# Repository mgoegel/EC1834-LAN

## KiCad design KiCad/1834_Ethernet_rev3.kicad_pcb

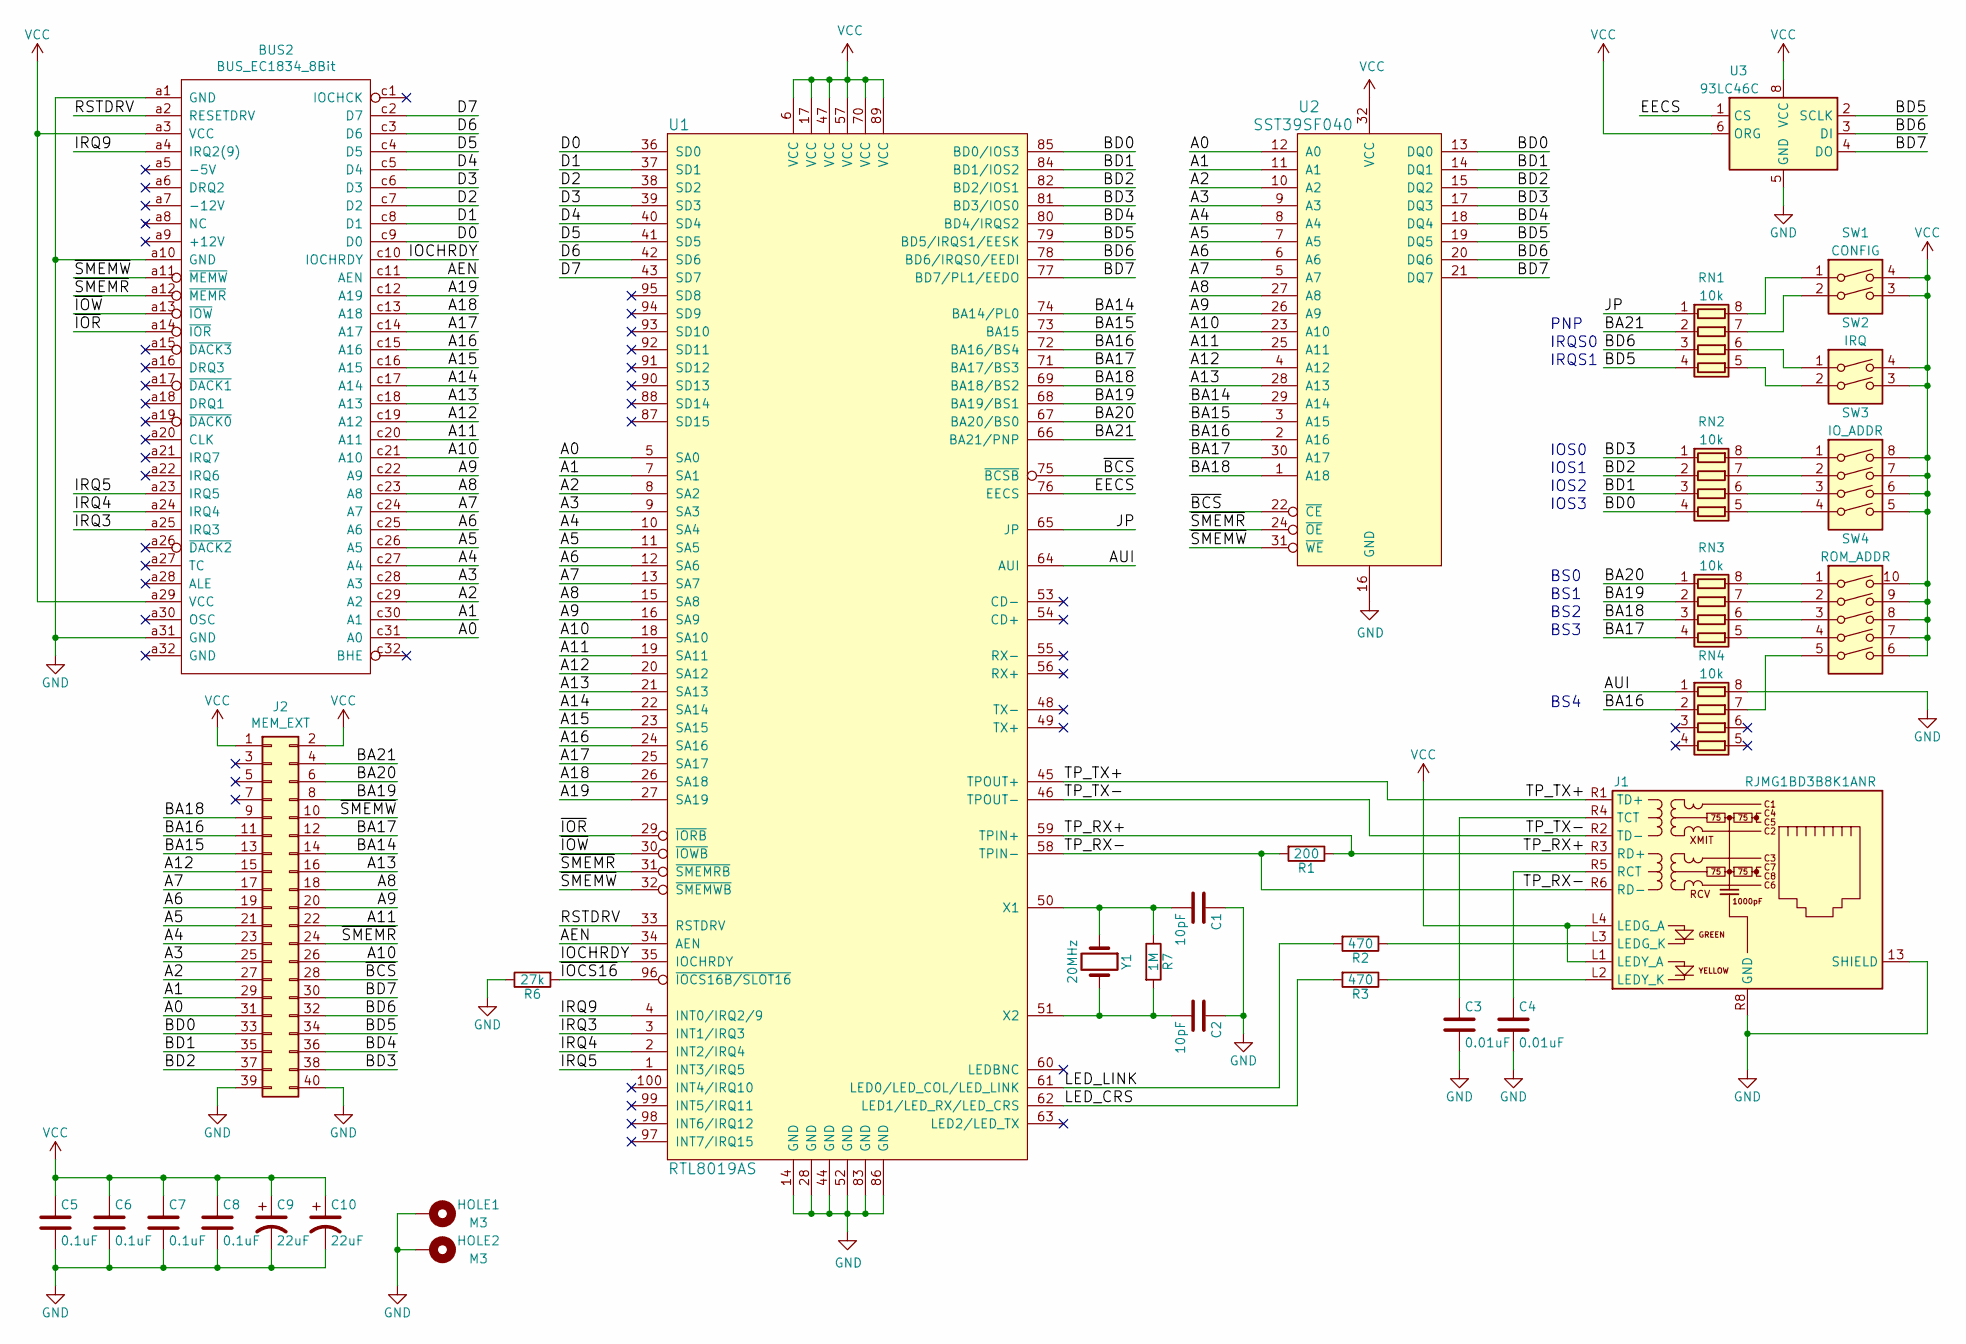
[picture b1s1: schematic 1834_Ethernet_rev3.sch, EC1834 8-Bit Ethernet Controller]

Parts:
BUS2: BUS_EC1834_8Bit; DIN41612_C_3x32_Male_Horizontal_THT
C1, C2: 10pF; C_0603_1608Metric_Pad1.08x0.95mm_HandSolder
C3, C4: 0.01uF; C_0603_1608Metric_Pad1.08x0.95mm_HandSolder
C5, C6, C7, C8: 0.1uF; C_0603_1608Metric_Pad1.08x0.95mm_HandSolder
C9, C10: 22uF; CP_EIA-3528-15_AVX-H_Pad1.50x2.35mm_HandSolder
HOLE1, HOLE2: M3; MountingHole_3.2mm_M3_Pad_Via
J1: RJMG1BD3B8K1ANR; RJ45_Amphenol_RJMG1BD3B8K1ANR
J2: MEM_EXT; Conn_Pin_Header_20x2_2.54mm
R1: 200; R_0603_1608Metric_Pad0.98x0.95mm_HandSolder
R2, R3: 470; R_0603_1608Metric_Pad0.98x0.95mm_HandSolder
R6: 27k; R_0603_1608Metric_Pad0.98x0.95mm_HandSolder
R7: 1M; R_0603_1608Metric_Pad0.98x0.95mm_HandSolder
RN1, RN2, RN3, RN4: 10k; R_Array_Convex_4x0603
SW1: CONFIG; Switch_DIP_2_Positions
SW2: IRQ; Switch_DIP_2_Positions
SW3: IO_ADDR; Switch_DIP_4_Positions
SW4: ROM_ADDR; Switch_DIP_5_Positions
U1: RTL8019AS; IC_PQFP-100_14x20mm_P0.65mm_Hand_Soldering
U2: SST39SF040; Socket_DIP32_600
U3: 93LC46C; SO-8_3.9x4.9mm_P1.27mm
Y1: 20MHz; Crystal_HC-49U_Vert

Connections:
/A0: BUS2.c31 (A0), J2.31, U1.5 (SA0), U2.12 (A0)
/A1: BUS2.c30 (A1), J2.29, U1.7 (SA1), U2.11 (A1)
/A2: BUS2.c29 (A2), J2.27, U1.8 (SA2), U2.10 (A2)
/A3: BUS2.c28 (A3), J2.25, U1.9 (SA3), U2.9 (A3)
/A4: BUS2.c27 (A4), J2.23, U1.10 (SA4), U2.8 (A4)
/A5: BUS2.c26 (A5), J2.21, U1.11 (SA5), U2.7 (A5)
/A6: BUS2.c25 (A6), J2.19, U1.12 (SA6), U2.6 (A6)
/A7: BUS2.c24 (A7), J2.17, U1.13 (SA7), U2.5 (A7)
/A8: BUS2.c23 (A8), J2.18, U1.15 (SA8), U2.27 (A8)
/A9: BUS2.c22 (A9), J2.20, U1.16 (SA9), U2.26 (A9)
/A10: BUS2.c21 (A10), J2.26, U1.18 (SA10), U2.23 (A10)
/A11: BUS2.c20 (A11), J2.22, U1.19 (SA11), U2.25 (A11)
/A12: BUS2.c19 (A12), J2.15, U1.20 (SA12), U2.4 (A12)
/A13: BUS2.c18 (A13), J2.16, U1.21 (SA13), U2.28 (A13)
/A14: BUS2.c17 (A14), U1.22 (SA14)
/A15: BUS2.c16 (A15), U1.23 (SA15)
/A16: BUS2.c15 (A16), U1.24 (SA16)
/A17: BUS2.c14 (A17), U1.25 (SA17)
/A18: BUS2.c13 (A18), U1.26 (SA18)
/A19: BUS2.c12 (A19), U1.27 (SA19)
/AEN: BUS2.c11 (AEN), U1.34 (AEN)
/AUI: RN4.1 (R1.1), U1.64 (AUI)
/BA14: J2.14, U1.74 (BA14/PL0), U2.29 (A14)
/BA15: J2.13, U1.73 (BA15), U2.3 (A15)
/BA16: J2.11, RN4.2 (R2.1), U1.72 (BA16/BS4), U2.2 (A16)
/BA17: J2.12, RN3.4 (R4.1), U1.71 (BA17/BS3), U2.30 (A17)
/BA18: J2.9, RN3.3 (R3.1), U1.69 (BA18/BS2), U2.1 (A18)
/BA19: J2.8, RN3.2 (R2.1), U1.68 (BA19/BS1)
/BA20: J2.6, RN3.1 (R1.1), U1.67 (BA20/BS0)
/BA21: J2.4, RN1.2 (R2.1), U1.66 (BA21/PNP)
/BD0: J2.33, RN2.4 (R4.1), U1.85 (BD0/IOS3), U2.13 (DQ0)
/BD1: J2.35, RN2.3 (R3.1), U1.84 (BD1/IOS2), U2.14 (DQ1)
/BD2: J2.37, RN2.2 (R2.1), U1.82 (BD2/IOS1), U2.15 (DQ2)
/BD3: J2.38, RN2.1 (R1.1), U1.81 (BD3/IOS0), U2.17 (DQ3)
/BD4: J2.36, U1.80 (BD4/IRQS2), U2.18 (DQ4)
/BD5: J2.34, RN1.4 (R4.1), U1.79 (BD5/IRQS1/EESK), U2.19 (DQ5), U3.2 (SCLK)
/BD6: J2.32, RN1.3 (R3.1), U1.78 (BD6/IRQS0/EEDI), U2.20 (DQ6), U3.3 (DI)
/BD7: J2.30, U1.77 (BD7/PL1/EEDO), U2.21 (DQ7), U3.4 (DO)
/D0: BUS2.c9 (D0), U1.36 (SD0)
/D1: BUS2.c8 (D1), U1.37 (SD1)
/D2: BUS2.c7 (D2), U1.38 (SD2)
/D3: BUS2.c6 (D3), U1.39 (SD3)
/D4: BUS2.c5 (D4), U1.40 (SD4)
/D5: BUS2.c4 (D5), U1.41 (SD5)
/D6: BUS2.c3 (D6), U1.42 (SD6)
/D7: BUS2.c2 (D7), U1.43 (SD7)
/EECS: U1.76 (EECS), U3.1 (CS)
/IOCHRDY: BUS2.c10 (IOCHRDY), U1.35 (IOCHRDY)
/IRQ3: BUS2.a25 (IRQ3), U1.3 (INT1/IRQ3)
/IRQ4: BUS2.a24 (IRQ4), U1.2 (INT2/IRQ4)
/IRQ5: BUS2.a23 (IRQ5), U1.1 (INT3/IRQ5)
/IRQ9: BUS2.a4 (IRQ2(9)), U1.4 (INT0/IRQ2/9)
/JP: RN1.1 (R1.1), U1.65 (JP)
/LED_CRS: R3.2, U1.62 (LED1/LED_RX/LED_CRS)
/LED_LINK: R2.2, U1.61 (LED0/LED_COL/LED_LINK)
/RSTDRV: BUS2.a2 (RESETDRV), U1.33 (RSTDRV)
/TP_RX+: J1.R3 (RD+), R1.1, U1.59 (TPIN+)
/TP_RX-: J1.R6 (RD-), R1.2, U1.58 (TPIN-)
/TP_TX+: J1.R1 (TD+), U1.45 (TPOUT+)
/TP_TX-: J1.R2 (TD-), U1.46 (TPOUT-)
/~BCS: J2.28, U1.75 (~BCSB), U2.22 (~CE)
/~IOCS16: R6.2, U1.96 (~IOCS16B/SLOT16)
/~IOR: BUS2.a14 (~IOR), U1.29 (~IORB)
/~IOW: BUS2.a13 (~IOW), U1.30 (~IOWB)
/~SMEMR: BUS2.a12 (~MEMR), J2.24, U1.31 (~SMEMRB), U2.24 (~OE)
/~SMEMW: BUS2.a11 (~MEMW), J2.10, U1.32 (~SMEMWB), U2.31 (~WE)
GND: BUS2.a1 (GND), BUS2.a10 (GND), BUS2.a31 (GND), C1.1, C2.1, C3.2, C4.2, C5.2, C6.2, C7.2, C8.2, C9.2, C10.2, HOLE1.1, HOLE2.1, J1.13 (SHIELD), J1.R8 (GND), J2.39, J2.40, R6.1, RN4.8 (R1.2), U1.14 (GND), U1.28 (GND), U1.44 (GND), U1.52 (GND), U1.83 (GND), U1.86 (GND), U2.16 (GND), U3.5 (GND)
unnamed: C1.2, R7.1, U1.50 (X1), Y1.1
unnamed: C2.2, R7.2, U1.51 (X2), Y1.2
unnamed: C3.1, J1.R4 (TCT)
unnamed: C4.1, J1.R5 (RCT)
unnamed: J1.L2 (LEDY_K), R3.1
unnamed: J1.L3 (LEDG_K), R2.1
unnamed: RN1.5 (R4.2), SW2.2
unnamed: RN1.6 (R3.2), SW2.1
unnamed: RN1.7 (R2.2), SW1.2
unnamed: RN1.8 (R1.2), SW1.1
unnamed: RN2.5 (R4.2), SW3.4
unnamed: RN2.6 (R3.2), SW3.3
unnamed: RN2.7 (R2.2), SW3.2
unnamed: RN2.8 (R1.2), SW3.1
unnamed: RN3.5 (R4.2), SW4.4
unnamed: RN3.6 (R3.2), SW4.3
unnamed: RN3.7 (R2.2), SW4.2
unnamed: RN3.8 (R1.2), SW4.1
unnamed: RN4.7 (R2.2), SW4.5
VCC: BUS2.a3 (VCC), BUS2.a29 (VCC), C5.1, C6.1, C7.1, C8.1, C9.1, C10.1, J1.L1 (LEDY_A), J1.L4 (LEDG_A), J2.1, J2.2, SW1.3, SW1.4, SW2.3, SW2.4, SW3.5, SW3.6, SW3.7, SW3.8, SW4.6, SW4.7, SW4.8, SW4.9, SW4.10, U1.6 (VCC), U1.17 (VCC), U1.47 (VCC), U1.57 (VCC), U1.70 (VCC), U1.89 (VCC), U2.32 (VCC), U3.6 (ORG), U3.8 (VCC)

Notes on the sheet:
IOS0
IOS1
IOS2
IOS3
IRQS0
IRQS1
BS4
BS3
BS2
BS1
BS0
PNP

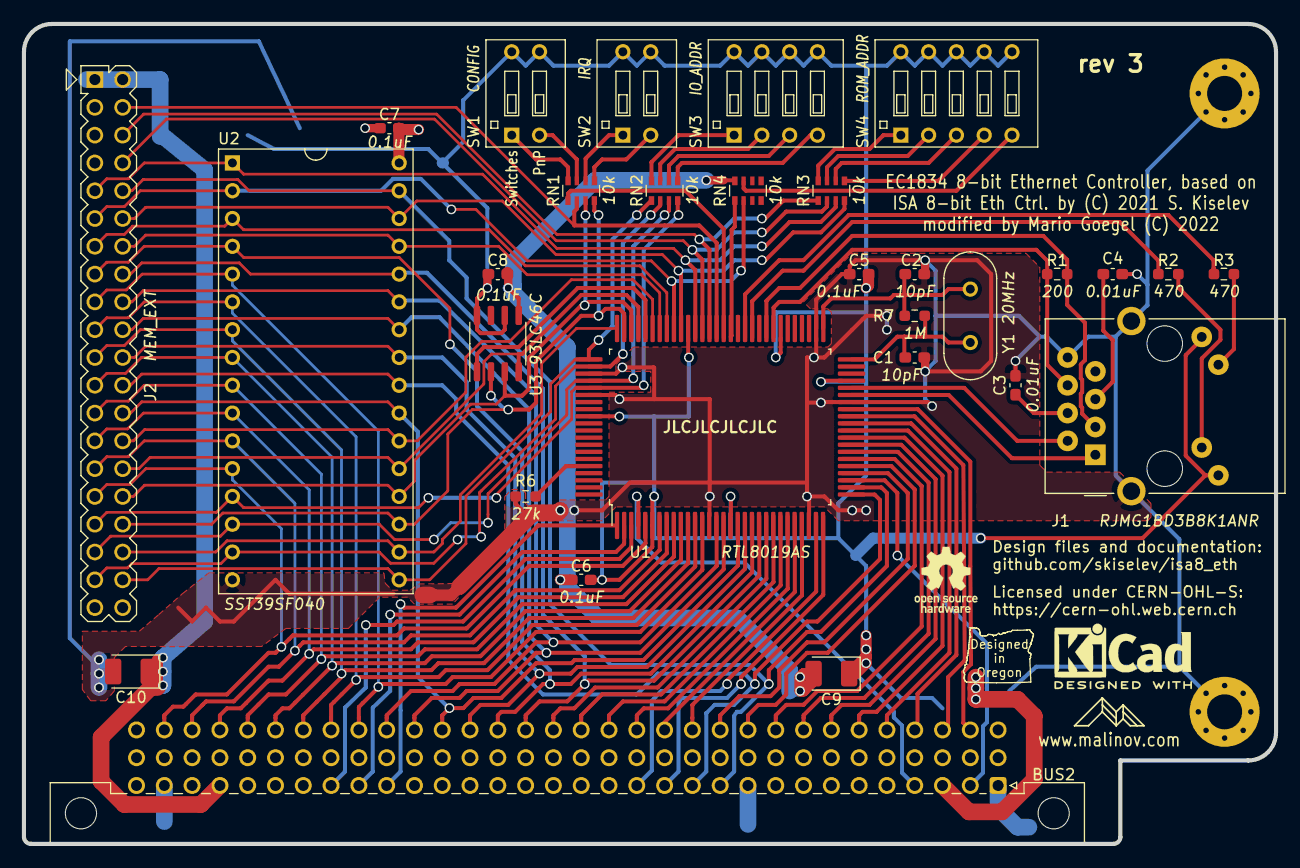
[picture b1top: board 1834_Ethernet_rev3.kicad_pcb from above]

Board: 2 copper layers, 114.4 x 74.9 mm, 32 parts (0 on the bottom side), 87 nets.

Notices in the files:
KiCad/1834_Ethernet_rev3.kicad_pcb:
Licensed under CERN-OHL-S: https://cern-ohl.web.cern.ch
ISA 8-bit Eth Ctrl. by (C) 2021 S. Kiselev
modified by Mario Goegel (C) 2022
